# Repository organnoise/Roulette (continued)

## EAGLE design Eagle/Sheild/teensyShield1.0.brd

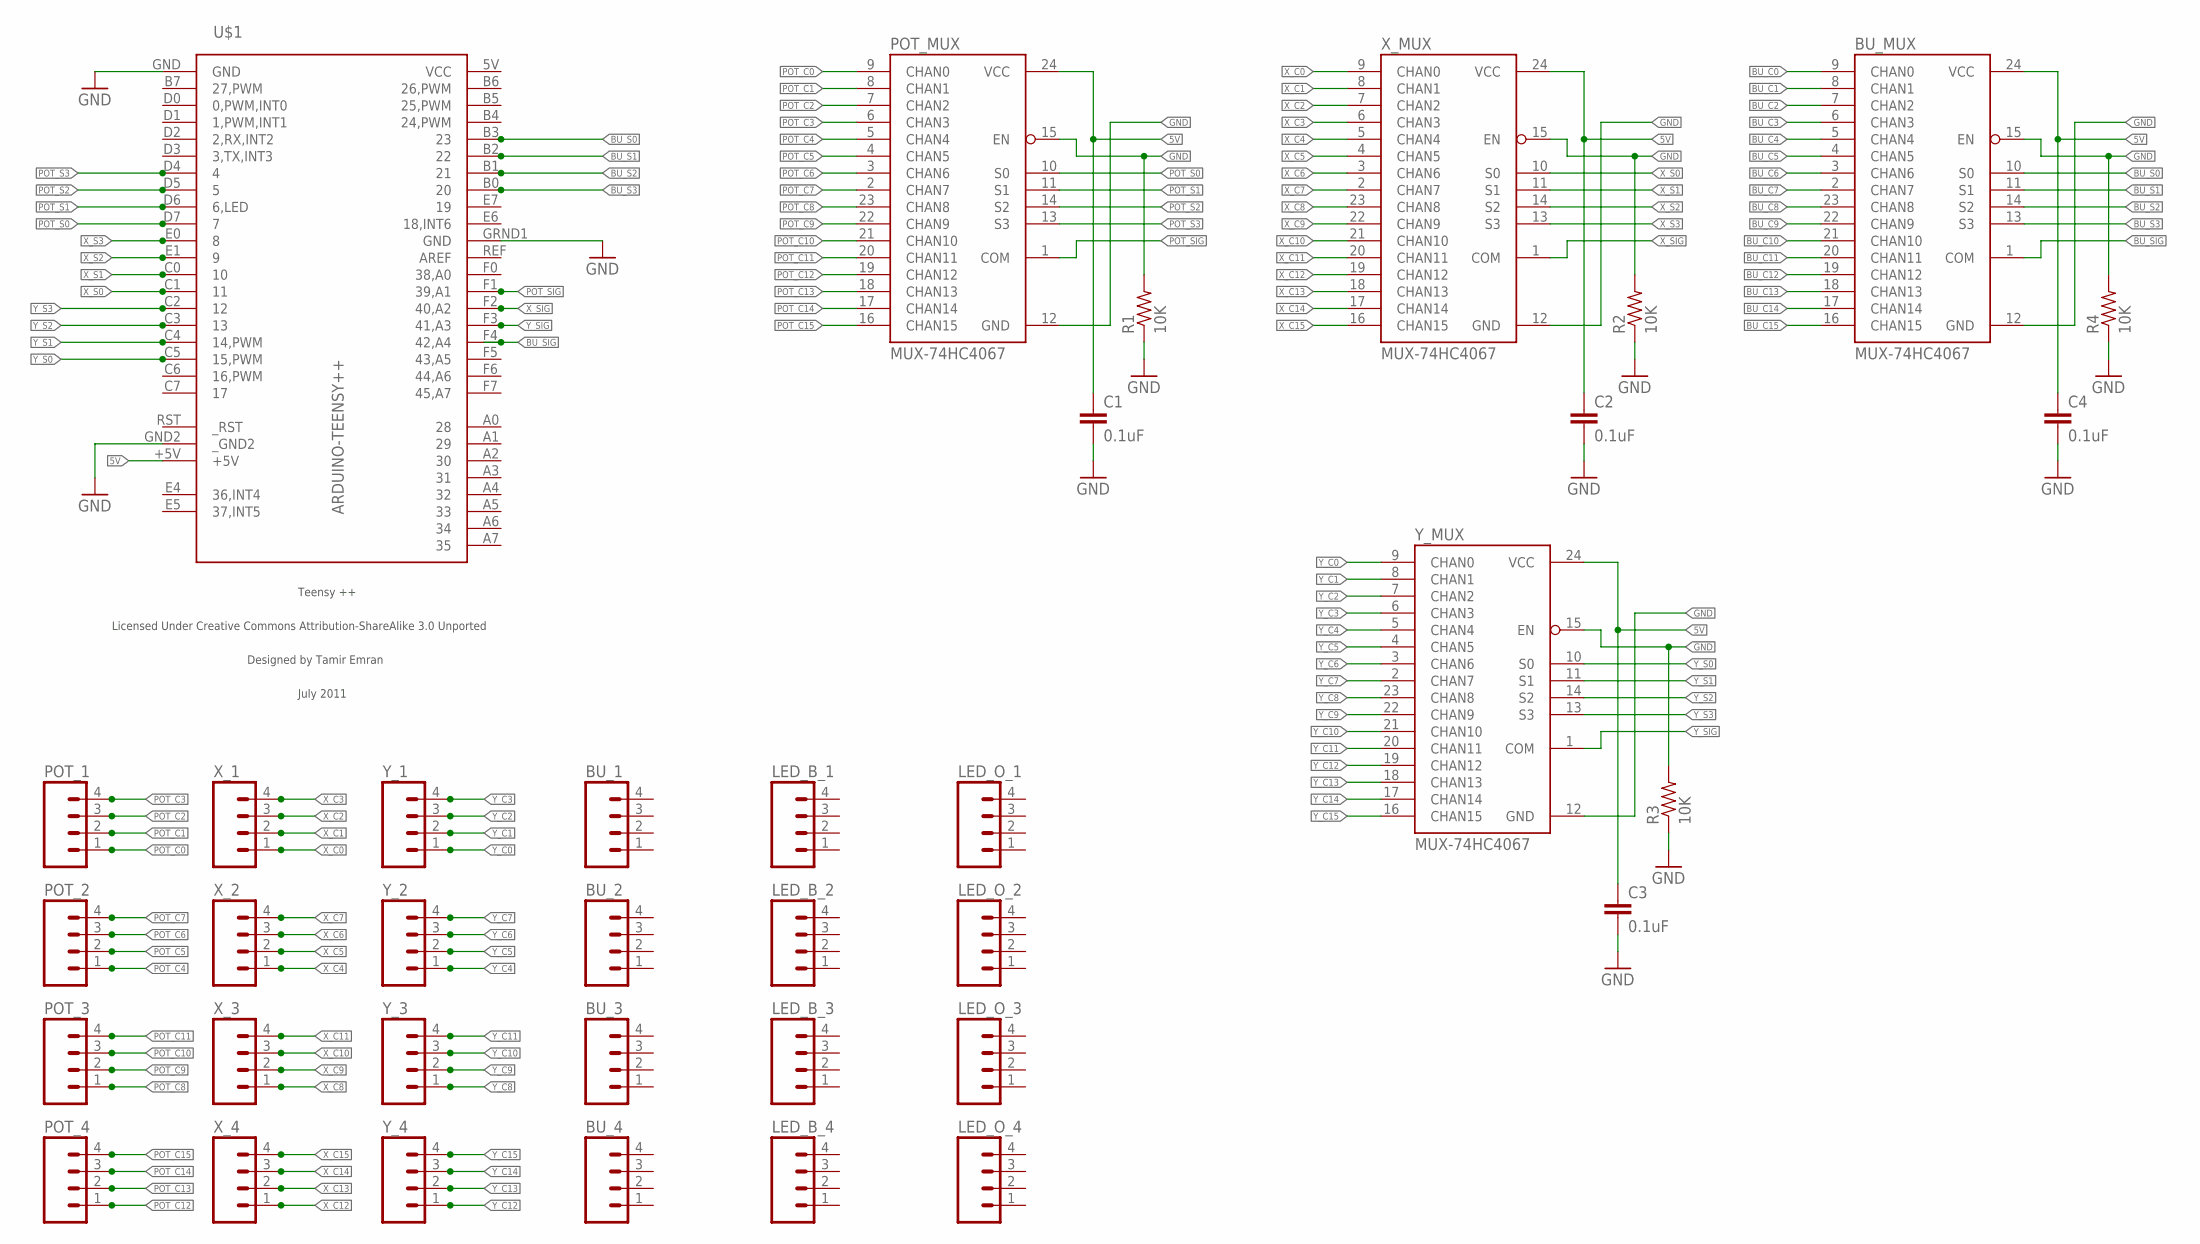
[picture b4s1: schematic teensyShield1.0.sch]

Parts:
BU_1, BU_2, BU_3, BU_4: M04NO_SILK_ALL_ROUND; 1X04_NO_SILK_ALL_ROUND
BU_MUX: MUX-74HC4067; SSOP24
C1, C2, C3, C4: 0.1uF; 0603
LED_B_1, LED_B_2, LED_B_3, LED_B_4: M04NO_SILK_ALL_ROUND; 1X04_NO_SILK_ALL_ROUND
LED_O_1, LED_O_2, LED_O_3, LED_O_4: M04NO_SILK_ALL_ROUND; 1X04_NO_SILK_ALL_ROUND
POT_1, POT_2, POT_3, POT_4: M04NO_SILK_ALL_ROUND; 1X04_NO_SILK_ALL_ROUND
POT_MUX: MUX-74HC4067; SSOP24
R1, R2, R3, R4: 10K; 0603
U$1: ARDUINO-TEENSY++; TEENSY++
X_1, X_2, X_3, X_4: M04NO_SILK_ALL_ROUND; 1X04_NO_SILK_ALL_ROUND
X_MUX: MUX-74HC4067; SSOP24
Y_1, Y_2, Y_3, Y_4: M04NO_SILK_ALL_ROUND; 1X04_NO_SILK_ALL_ROUND
Y_MUX: MUX-74HC4067; SSOP24

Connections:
5V: BU_MUX.24 (VCC), C1.1, C2.1, C3.1, C4.1, POT_MUX.24 (VCC), X_MUX.24 (VCC), Y_MUX.24 (VCC)
BU_C0: BU_MUX.9 (CHAN0)
BU_C1: BU_MUX.8 (CHAN1)
BU_C2: BU_MUX.7 (CHAN2)
BU_C3: BU_MUX.6 (CHAN3)
BU_C4: BU_MUX.5 (CHAN4)
BU_C5: BU_MUX.4 (CHAN5)
BU_C6: BU_MUX.3 (CHAN6)
BU_C7: BU_MUX.2 (CHAN7)
BU_C8: BU_MUX.23 (CHAN8)
BU_C9: BU_MUX.22 (CHAN9)
BU_C10: BU_MUX.21 (CHAN10)
BU_C11: BU_MUX.20 (CHAN11)
BU_C12: BU_MUX.19 (CHAN12)
BU_C13: BU_MUX.18 (CHAN13)
BU_C14: BU_MUX.17 (CHAN14)
BU_C15: BU_MUX.16 (CHAN15)
BU_S0: BU_MUX.10 (S0), U$1.B3 (23)
BU_S1: BU_MUX.11 (S1), U$1.B2 (22)
BU_S2: BU_MUX.14 (S2), U$1.B1 (21)
BU_S3: BU_MUX.13 (S3), U$1.B0 (20)
BU_SIG: BU_MUX.1 (COM), U$1.F4 (42,A4)
GND: BU_MUX.12 (GND), BU_MUX.15 (EN), C1.2, C2.2, C3.2, C4.2, POT_MUX.12 (GND), POT_MUX.15 (EN), R1.1, R1.2, R2.1, R2.2, R3.1, R3.2, R4.1, R4.2, U$1.GND, U$1.GND2 (_GND2), U$1.GRND1 (GND), X_MUX.12 (GND), X_MUX.15 (EN), Y_MUX.12 (GND), Y_MUX.15 (EN)
POT_C0: POT_1.1, POT_MUX.9 (CHAN0)
POT_C1: POT_1.2, POT_MUX.8 (CHAN1)
POT_C2: POT_1.3, POT_MUX.7 (CHAN2)
POT_C3: POT_1.4, POT_MUX.6 (CHAN3)
POT_C4: POT_2.1, POT_MUX.5 (CHAN4)
POT_C5: POT_2.2, POT_MUX.4 (CHAN5)
POT_C6: POT_2.3, POT_MUX.3 (CHAN6)
POT_C7: POT_2.4, POT_MUX.2 (CHAN7)
POT_C8: POT_3.1, POT_MUX.23 (CHAN8)
POT_C9: POT_3.2, POT_MUX.22 (CHAN9)
POT_C10: POT_3.3, POT_MUX.21 (CHAN10)
POT_C11: POT_3.4, POT_MUX.20 (CHAN11)
POT_C12: POT_4.1, POT_MUX.19 (CHAN12)
POT_C13: POT_4.2, POT_MUX.18 (CHAN13)
POT_C14: POT_4.3, POT_MUX.17 (CHAN14)
POT_C15: POT_4.4, POT_MUX.16 (CHAN15)
POT_S0: POT_MUX.10 (S0), U$1.D7 (7)
POT_S1: POT_MUX.11 (S1), U$1.D6 (6,LED)
POT_S2: POT_MUX.14 (S2), U$1.D5 (5)
POT_S3: POT_MUX.13 (S3), U$1.D4 (4)
POT_SIG: POT_MUX.1 (COM)
VCC: U$1.5V (VCC)
X_C0: X_1.1, X_MUX.9 (CHAN0)
X_C1: X_1.2, X_MUX.8 (CHAN1)
X_C2: X_1.3, X_MUX.7 (CHAN2)
X_C3: X_1.4, X_MUX.6 (CHAN3)
X_C4: X_2.1, X_MUX.5 (CHAN4)
X_C5: X_2.2, X_MUX.4 (CHAN5)
X_C6: X_2.3, X_MUX.3 (CHAN6)
X_C7: X_2.4, X_MUX.2 (CHAN7)
X_C8: X_3.1, X_MUX.23 (CHAN8)
X_C9: X_3.2, X_MUX.22 (CHAN9)
X_C10: X_3.3, X_MUX.21 (CHAN10)
X_C11: X_3.4, X_MUX.20 (CHAN11)
X_C12: X_4.1, X_MUX.19 (CHAN12)
X_C13: X_4.2, X_MUX.18 (CHAN13)
X_C14: X_4.3, X_MUX.17 (CHAN14)
X_C15: X_4.4, X_MUX.16 (CHAN15)
X_S0: U$1.C1 (11), X_MUX.10 (S0)
X_S1: U$1.C0 (10), X_MUX.11 (S1)
X_S2: U$1.E1 (9), X_MUX.14 (S2)
X_S3: U$1.E0 (8), X_MUX.13 (S3)
X_SIG: X_MUX.1 (COM)
Y_C0: Y_1.1, Y_MUX.9 (CHAN0)
Y_C1: Y_1.2, Y_MUX.8 (CHAN1)
Y_C2: Y_1.3, Y_MUX.7 (CHAN2)
Y_C3: Y_1.4, Y_MUX.6 (CHAN3)
Y_C4: Y_2.1, Y_MUX.5 (CHAN4)
Y_C5: Y_2.2, Y_MUX.4 (CHAN5)
Y_C6: Y_2.3, Y_MUX.3 (CHAN6)
Y_C7: Y_2.4, Y_MUX.2 (CHAN7)
Y_C8: Y_3.1, Y_MUX.23 (CHAN8)
Y_C9: Y_3.2, Y_MUX.22 (CHAN9)
Y_C10: Y_3.3, Y_MUX.21 (CHAN10)
Y_C11: Y_3.4, Y_MUX.20 (CHAN11)
Y_C12: Y_4.1, Y_MUX.19 (CHAN12)
Y_C13: Y_4.2, Y_MUX.18 (CHAN13)
Y_C14: Y_4.3, Y_MUX.17 (CHAN14)
Y_C15: Y_4.4, Y_MUX.16 (CHAN15)
Y_S0: U$1.C5 (15,PWM), Y_MUX.10 (S0)
Y_S1: U$1.C4 (14,PWM), Y_MUX.11 (S1)
Y_S2: U$1.C3 (13), Y_MUX.14 (S2)
Y_S3: U$1.C2 (12), Y_MUX.13 (S3)
Y_SIG: U$1.F3 (41,A3), Y_MUX.1 (COM)

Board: 2 copper layers, 37 parts (0 on the bottom side), 68 nets, no tracks yet.

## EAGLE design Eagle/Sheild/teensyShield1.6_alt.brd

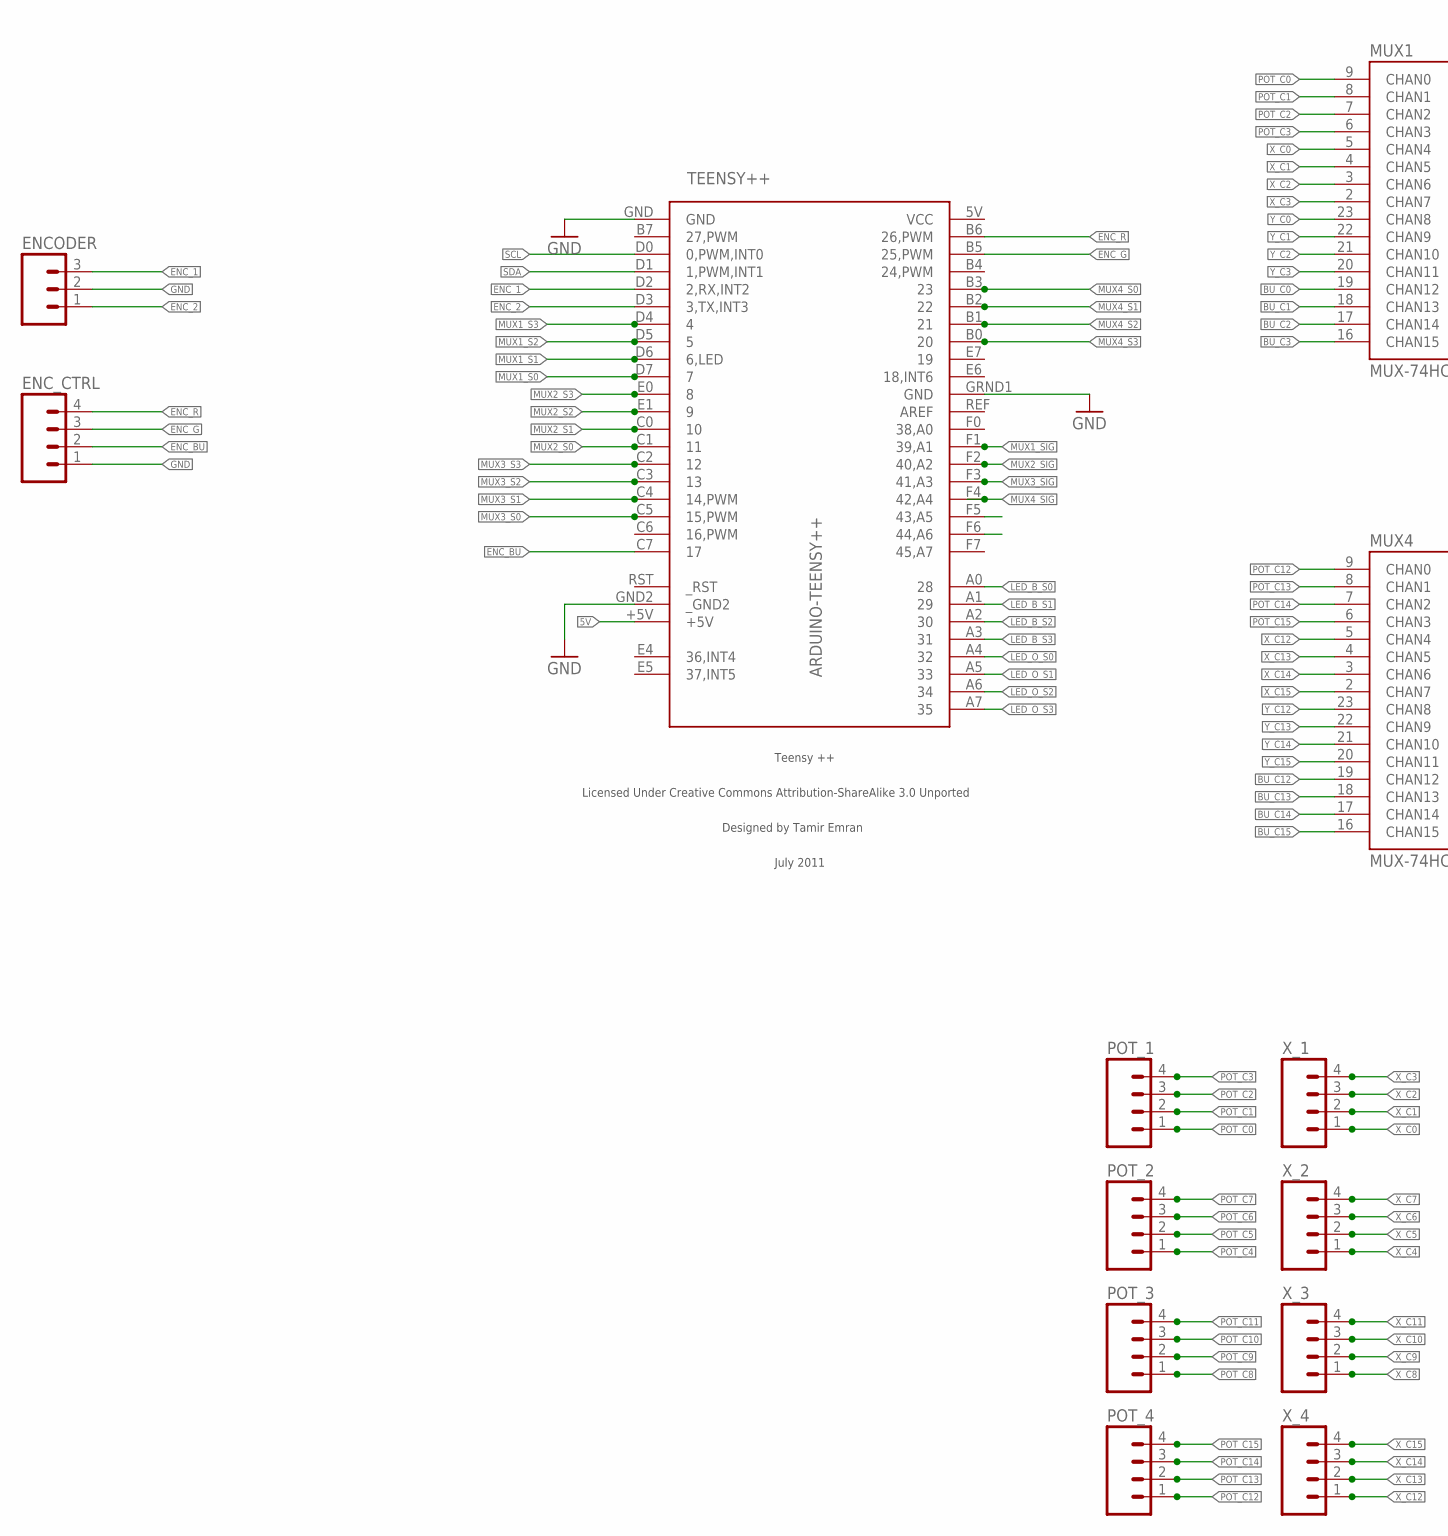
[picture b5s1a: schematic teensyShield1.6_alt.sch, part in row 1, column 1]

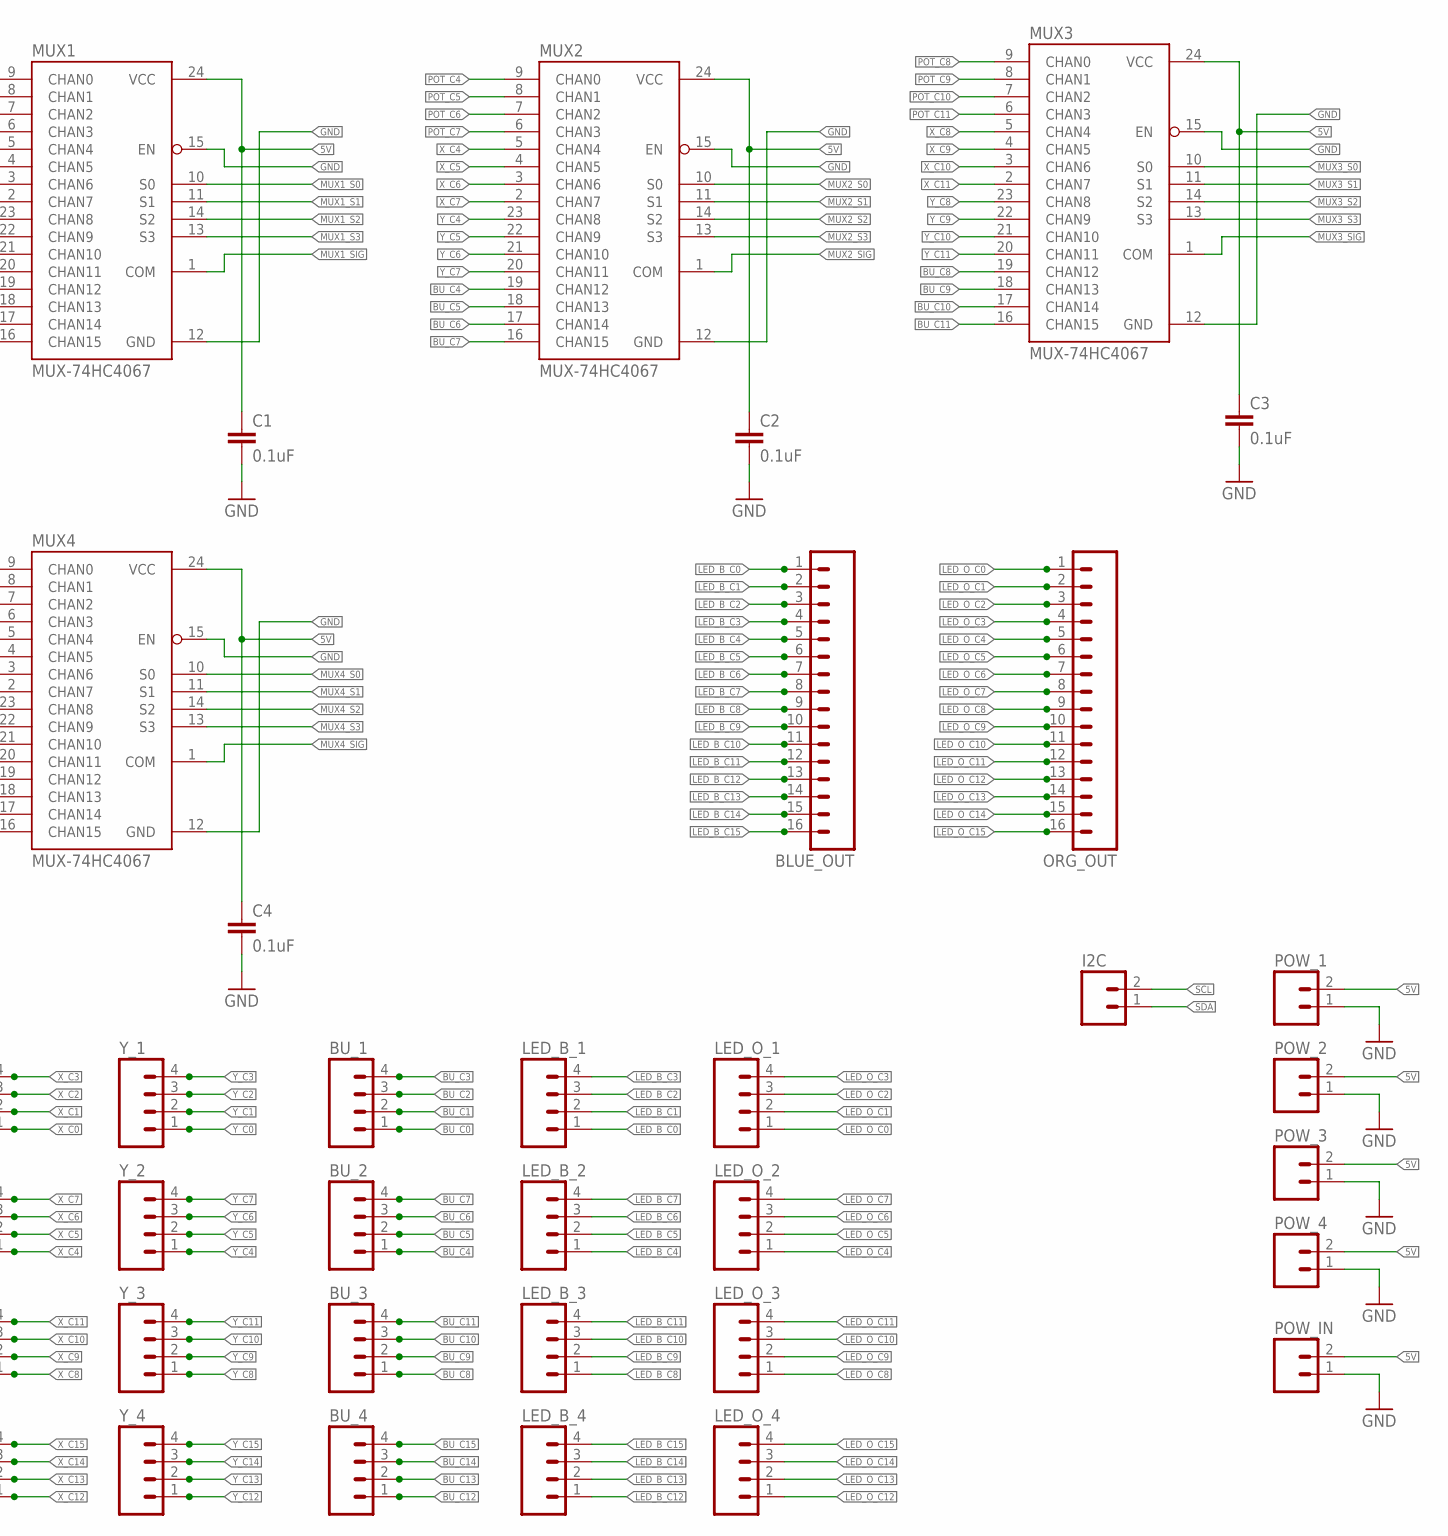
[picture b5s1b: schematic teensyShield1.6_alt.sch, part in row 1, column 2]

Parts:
BLUE_OUT: M161X16_NO_SILK; 1X16_NO_SILK
BU_1, BU_2, BU_3, BU_4: M04NO_SILK_ALL_ROUND; 1X04_NO_SILK_ALL_ROUND
C1, C2, C3, C4: 0.1uF; 0603
ENCODER: M031X03_NO_SILK; 1X03_NO_SILK
ENC_CTRL: M041X04_NO_SILK; 1X04_NO_SILK
I2C: M02LOCK; 1X02_LOCK
LED_B_1, LED_B_2, LED_B_3, LED_B_4: M04NO_SILK_ALL_ROUND; 1X04_NO_SILK_ALL_ROUND
LED_O_1, LED_O_2, LED_O_3, LED_O_4: M04NO_SILK_ALL_ROUND; 1X04_NO_SILK_ALL_ROUND
MUX1, MUX2, MUX3, MUX4: MUX-74HC4067; SSOP24
ORG_OUT: M161X16_NO_SILK; 1X16_NO_SILK
POT_1, POT_2, POT_3, POT_4: M04NO_SILK_ALL_ROUND; 1X04_NO_SILK_ALL_ROUND
POW_1, POW_2, POW_3, POW_4: M02POLAR; MOLEX-1X2
POW_IN: M02POLAR; MOLEX-1X2
TEENSY++: ARDUINO-TEENSY++; TEENSY++
X_1, X_2, X_3, X_4: M04NO_SILK_ALL_ROUND; 1X04_NO_SILK_ALL_ROUND
Y_1, Y_2, Y_3, Y_4: M04NO_SILK_ALL_ROUND; 1X04_NO_SILK_ALL_ROUND

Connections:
5V: C1.1, C2.1, C3.1, C4.1, MUX1.24 (VCC), MUX2.24 (VCC), MUX3.24 (VCC), MUX4.24 (VCC), POW_1.2, POW_2.2, POW_3.2, POW_4.2, POW_IN.2
BU_C0: BU_1.1, MUX1.19 (CHAN12)
BU_C1: BU_1.2, MUX1.18 (CHAN13)
BU_C2: BU_1.3, MUX1.17 (CHAN14)
BU_C3: BU_1.4, MUX1.16 (CHAN15)
BU_C4: BU_2.1, MUX2.19 (CHAN12)
BU_C5: BU_2.2, MUX2.18 (CHAN13)
BU_C6: BU_2.3, MUX2.17 (CHAN14)
BU_C7: BU_2.4, MUX2.16 (CHAN15)
BU_C8: BU_3.1, MUX3.19 (CHAN12)
BU_C9: BU_3.2, MUX3.18 (CHAN13)
BU_C10: BU_3.3, MUX3.17 (CHAN14)
BU_C11: BU_3.4, MUX3.16 (CHAN15)
BU_C12: BU_4.1, MUX4.19 (CHAN12)
BU_C13: BU_4.2, MUX4.18 (CHAN13)
BU_C14: BU_4.3, MUX4.17 (CHAN14)
BU_C15: BU_4.4, MUX4.16 (CHAN15)
ENC_1: ENCODER.3, TEENSY++.D2 (2,RX,INT2)
ENC_2: ENCODER.1, TEENSY++.D3 (3,TX,INT3)
ENC_BU: ENC_CTRL.2, TEENSY++.C7 (17)
ENC_G: ENC_CTRL.3, TEENSY++.B5 (25,PWM)
ENC_R: ENC_CTRL.4, TEENSY++.B6 (26,PWM)
GND: C1.2, C2.2, C3.2, C4.2, ENCODER.2, ENC_CTRL.1, MUX1.12 (GND), MUX1.15 (EN), MUX2.12 (GND), MUX2.15 (EN), MUX3.12 (GND), MUX3.15 (EN), MUX4.12 (GND), MUX4.15 (EN), POW_1.1, POW_2.1, POW_3.1, POW_4.1, POW_IN.1, TEENSY++.GND, TEENSY++.GND2 (_GND2), TEENSY++.GRND1 (GND)
LED_B_C0: BLUE_OUT.1, LED_B_1.1
LED_B_C1: BLUE_OUT.2, LED_B_1.2
LED_B_C2: BLUE_OUT.3, LED_B_1.3
LED_B_C3: BLUE_OUT.4, LED_B_1.4
LED_B_C4: BLUE_OUT.5, LED_B_2.1
LED_B_C5: BLUE_OUT.6, LED_B_2.2
LED_B_C6: BLUE_OUT.7, LED_B_2.3
LED_B_C7: BLUE_OUT.8, LED_B_2.4
LED_B_C8: BLUE_OUT.9, LED_B_3.1
LED_B_C9: BLUE_OUT.10, LED_B_3.2
LED_B_C10: BLUE_OUT.11, LED_B_3.3
LED_B_C11: BLUE_OUT.12, LED_B_3.4
LED_B_C12: BLUE_OUT.13, LED_B_4.1
LED_B_C13: BLUE_OUT.14, LED_B_4.2
LED_B_C14: BLUE_OUT.15, LED_B_4.3
LED_B_C15: BLUE_OUT.16, LED_B_4.4
LED_B_S0: TEENSY++.A0 (28)
LED_B_S1: TEENSY++.A1 (29)
LED_B_S2: TEENSY++.A2 (30)
LED_B_S3: TEENSY++.A3 (31)
LED_O_C0: LED_O_1.1, ORG_OUT.1
LED_O_C1: LED_O_1.2, ORG_OUT.2
LED_O_C2: LED_O_1.3, ORG_OUT.3
LED_O_C3: LED_O_1.4, ORG_OUT.4
LED_O_C4: LED_O_2.1, ORG_OUT.5
LED_O_C5: LED_O_2.2, ORG_OUT.6
LED_O_C6: LED_O_2.3, ORG_OUT.7
LED_O_C7: LED_O_2.4, ORG_OUT.8
LED_O_C8: LED_O_3.1, ORG_OUT.9
LED_O_C9: LED_O_3.2, ORG_OUT.10
LED_O_C10: LED_O_3.3, ORG_OUT.11
LED_O_C11: LED_O_3.4, ORG_OUT.12
LED_O_C12: LED_O_4.1, ORG_OUT.13
LED_O_C13: LED_O_4.2, ORG_OUT.14
LED_O_C14: LED_O_4.3, ORG_OUT.15
LED_O_C15: LED_O_4.4, ORG_OUT.16
LED_O_S0: TEENSY++.A4 (32)
LED_O_S1: TEENSY++.A5 (33)
LED_O_S2: TEENSY++.A6 (34)
LED_O_S3: TEENSY++.A7 (35)
MUX1_S0: MUX1.10 (S0), TEENSY++.D7 (7)
MUX1_S1: MUX1.11 (S1), TEENSY++.D6 (6,LED)
MUX1_S2: MUX1.14 (S2), TEENSY++.D5 (5)
MUX1_S3: MUX1.13 (S3), TEENSY++.D4 (4)
MUX1_SIG: MUX1.1 (COM)
MUX2_S0: MUX2.10 (S0), TEENSY++.C1 (11)
MUX2_S1: MUX2.11 (S1), TEENSY++.C0 (10)
MUX2_S2: MUX2.14 (S2), TEENSY++.E1 (9)
MUX2_S3: MUX2.13 (S3), TEENSY++.E0 (8)
MUX2_SIG: MUX2.1 (COM)
MUX3_S0: MUX3.10 (S0), TEENSY++.C5 (15,PWM)
MUX3_S1: MUX3.11 (S1), TEENSY++.C4 (14,PWM)
MUX3_S2: MUX3.14 (S2), TEENSY++.C3 (13)
MUX3_S3: MUX3.13 (S3), TEENSY++.C2 (12)
MUX3_SIG: MUX3.1 (COM), TEENSY++.F3 (41,A3)
MUX4_S0: MUX4.10 (S0), TEENSY++.B3 (23)
MUX4_S1: MUX4.11 (S1), TEENSY++.B2 (22)
MUX4_S2: MUX4.14 (S2), TEENSY++.B1 (21)
MUX4_S3: MUX4.13 (S3), TEENSY++.B0 (20)
MUX4_SIG: MUX4.1 (COM), TEENSY++.F4 (42,A4)
POT_C0: MUX1.9 (CHAN0), POT_1.1
POT_C1: MUX1.8 (CHAN1), POT_1.2
POT_C2: MUX1.7 (CHAN2), POT_1.3
POT_C3: MUX1.6 (CHAN3), POT_1.4
POT_C4: MUX2.9 (CHAN0), POT_2.1
POT_C5: MUX2.8 (CHAN1), POT_2.2
POT_C6: MUX2.7 (CHAN2), POT_2.3
POT_C7: MUX2.6 (CHAN3), POT_2.4
POT_C8: MUX3.9 (CHAN0), POT_3.1
POT_C9: MUX3.8 (CHAN1), POT_3.2
POT_C10: MUX3.7 (CHAN2), POT_3.3
POT_C11: MUX3.6 (CHAN3), POT_3.4
POT_C12: MUX4.9 (CHAN0), POT_4.1
POT_C13: MUX4.8 (CHAN1), POT_4.2
POT_C14: MUX4.7 (CHAN2), POT_4.3
POT_C15: MUX4.6 (CHAN3), POT_4.4
SCL: I2C.2, TEENSY++.D0 (0,PWM,INT0)
SDA: I2C.1, TEENSY++.D1 (1,PWM,INT1)
VCC: TEENSY++.5V (VCC)
X_C0: MUX1.5 (CHAN4), X_1.1
X_C1: MUX1.4 (CHAN5), X_1.2
X_C2: MUX1.3 (CHAN6), X_1.3
X_C3: MUX1.2 (CHAN7), X_1.4
X_C4: MUX2.5 (CHAN4), X_2.1
X_C5: MUX2.4 (CHAN5), X_2.2
X_C6: MUX2.3 (CHAN6), X_2.3
X_C7: MUX2.2 (CHAN7), X_2.4
X_C8: MUX3.5 (CHAN4), X_3.1
X_C9: MUX3.4 (CHAN5), X_3.2
X_C10: MUX3.3 (CHAN6), X_3.3
X_C11: MUX3.2 (CHAN7), X_3.4
X_C12: MUX4.5 (CHAN4), X_4.1
X_C13: MUX4.4 (CHAN5), X_4.2
X_C14: MUX4.3 (CHAN6), X_4.3
X_C15: MUX4.2 (CHAN7), X_4.4
Y_C0: MUX1.23 (CHAN8), Y_1.1
Y_C1: MUX1.22 (CHAN9), Y_1.2
Y_C2: MUX1.21 (CHAN10), Y_1.3
Y_C3: MUX1.20 (CHAN11), Y_1.4
Y_C4: MUX2.23 (CHAN8), Y_2.1
Y_C5: MUX2.22 (CHAN9), Y_2.2
Y_C6: MUX2.21 (CHAN10), Y_2.3
Y_C7: MUX2.20 (CHAN11), Y_2.4
Y_C8: MUX3.23 (CHAN8), Y_3.1
Y_C9: MUX3.22 (CHAN9), Y_3.2
Y_C10: MUX3.21 (CHAN10), Y_3.3
Y_C11: MUX3.20 (CHAN11), Y_3.4
Y_C12: MUX4.23 (CHAN8), Y_4.1
Y_C13: MUX4.22 (CHAN9), Y_4.2
Y_C14: MUX4.21 (CHAN10), Y_4.3
Y_C15: MUX4.20 (CHAN11), Y_4.4

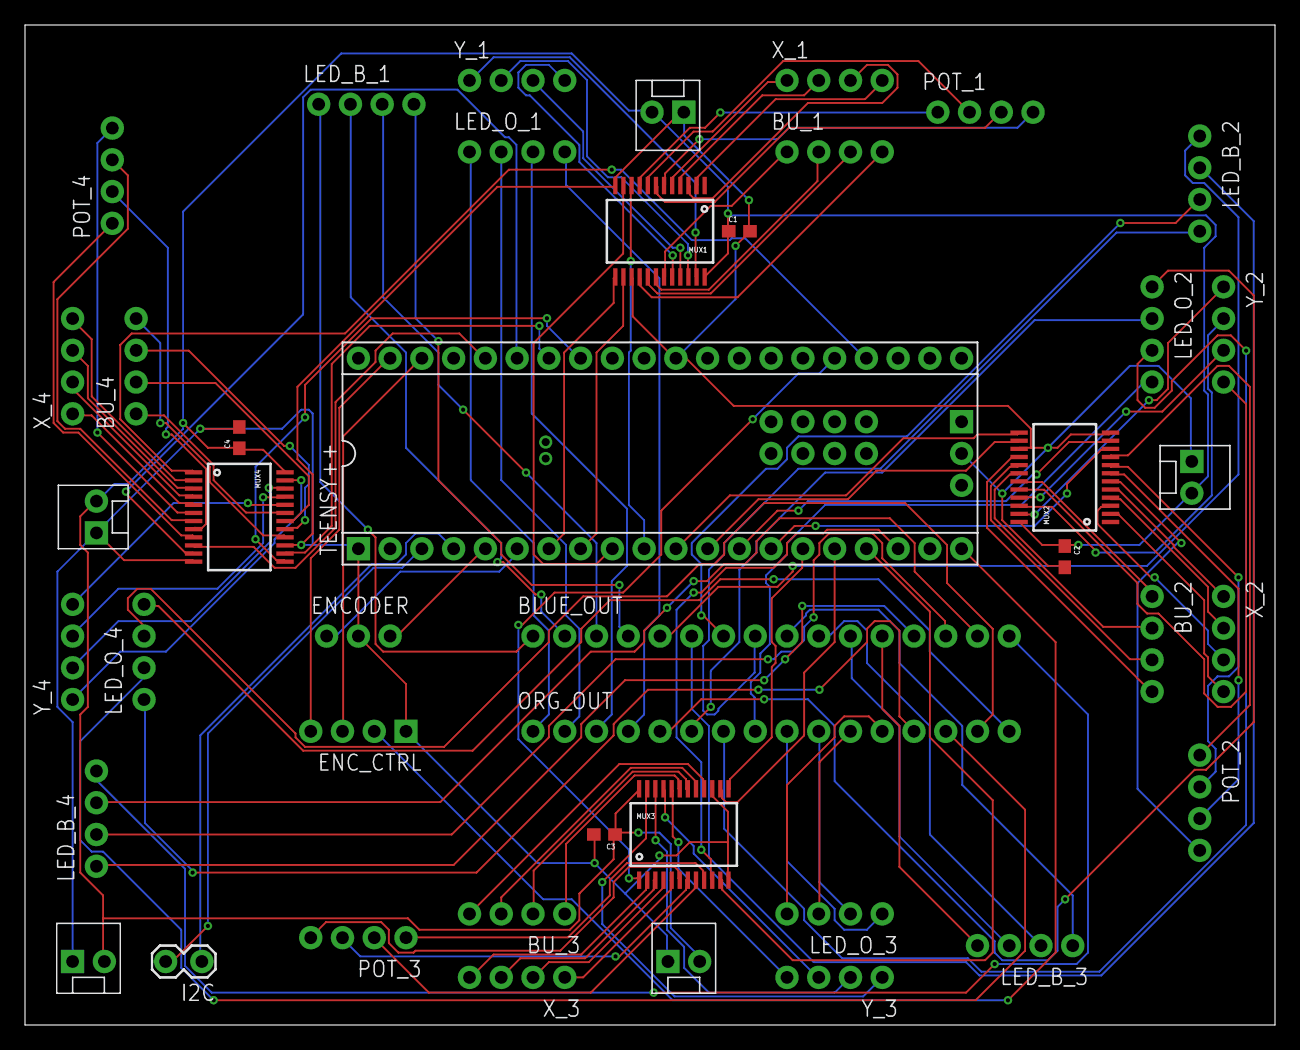
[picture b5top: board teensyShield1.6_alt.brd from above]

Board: 2 copper layers, 100.0 x 80.0 mm, 43 parts (0 on the bottom side), 123 nets.

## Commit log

2017-08-15 added eagle
2017-08-15 eagle cleanup
2017-08-15 rm stuff
2017-08-15 chuck and CAD
2017-08-15 pictures
2017-09-14 Arduino added
2018-01-09 preset studies
2018-01-11 presets
2018-01-13 encoder
2018-01-14 tap tempo
2018-01-16 offset
2018-01-18 preset loading
2021-10-12 Arduino etc.
